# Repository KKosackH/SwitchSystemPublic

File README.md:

# SwitchSystem  
**NOTE: Files with parts under NDA has been removed**

The **SwitchSystem** PCB was developed as an *add-on discharging solution* for existing **AC home chargers**.  

Although the concept worked, the product was ultimately deemed too **expensive** for production. As a result, the design has been made publicly available.  

All major components were tested and verified functional, including the **HomePlug Green PHY (PLC communication)** with negligible switching losses. However, the PCB was not fully finalized — see the [TO-DO](#to-do) list below for pending improvements.  

---

## Features  
- **Discharging add-on** for existing AC chargers  
- **PLC communication** via HomePlug Green PHY  
- **Integration with Raspberry Pi** through a 2×20 GPIO connector  
- **BatteryBridge compatibility** via JST connector  
- **External I/O**: LCD screen and buttons via JST  
- **Vehicle interface**: IEC 62196 Type 2 AC plug with temperature sensor and lock  
- **Inverter interface**: CANBus development board mounted on Raspberry Pi  

---

## Design Notes  
- The board was later split into multiple PCBs to:  
  - Avoid routing **AC mains** directly onto the main board  
  - Reduce **EMI issues**  
- The newer versions (under NDA) added advanced features such as:  
  - **LTE Cat 4 module**  
  - **CANBus support**  
  - **AMD Xilinx Zynq 7000 SoC**  

> ⚠️ If using the **BatteryBridge v2**, remove the `[3.4] DC-DC converter` and patch the **12 V output** of the BatteryBridge to the 12 V net on the SwitchSystem PCB.  

A full circuit description is available in the [Documentation folder](./Documentation).  

---

## Schematic & PCB  

The schematic is organized using hierarchical sheets, with the root page showing all user-interactable components.  

- **First page schematic**  

- **PCB Front**  

- **PCB Back**  

---

## TO-DO  
Remaining improvements for the PCB design:  

1. Add node names to all nets  
2. Ensure all schematic symbols have correct naming  
3. Add transfer vias  
4. Match SPI line lengths  
5. Change BatteryBridge connector to flat-flex  
6. Add new ADC and connect to motor measurement  
7. Add color coding for cables on PCB  
8. Add low-pass filter to CPRead ADC  
9. Add protected earth connector  
10. Add default charge state for power-loss events  
11. Adjust PCB size for mechanically stable Raspberry Pi mounting  

---

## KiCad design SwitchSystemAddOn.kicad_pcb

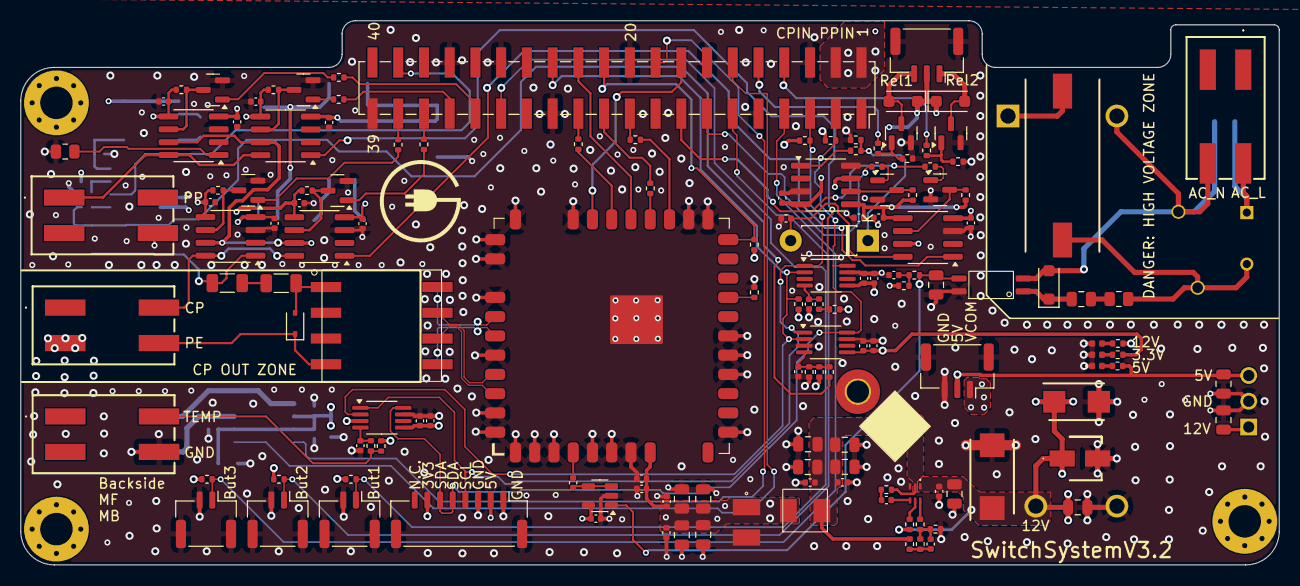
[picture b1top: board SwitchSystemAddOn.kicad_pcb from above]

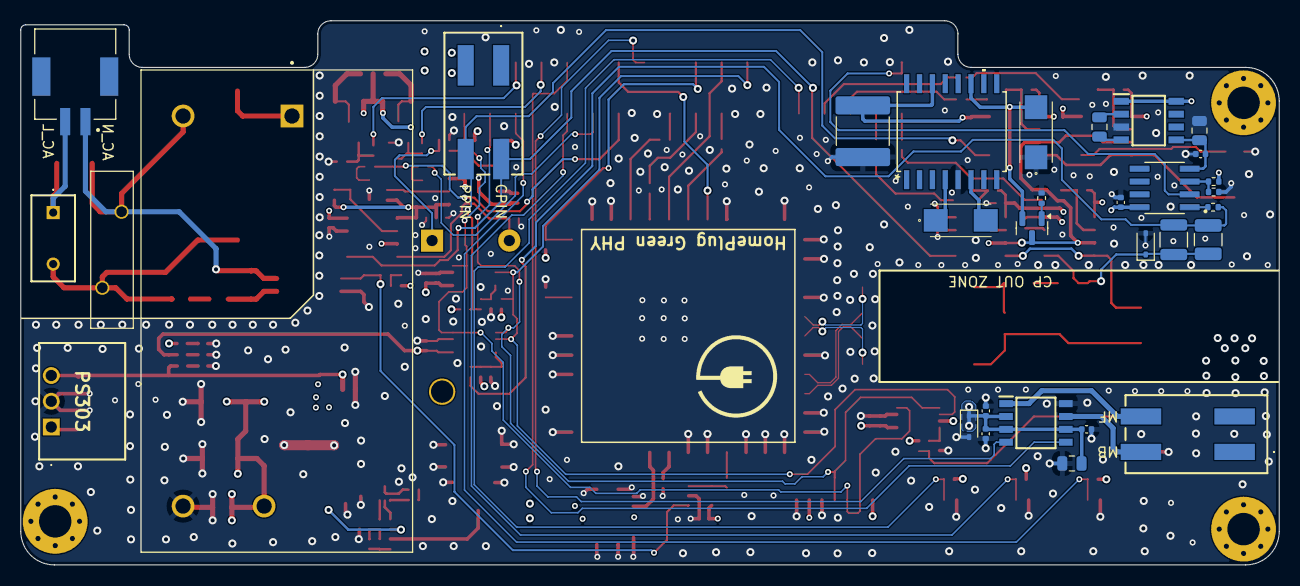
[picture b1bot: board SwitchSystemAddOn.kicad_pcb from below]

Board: 6 copper layers, 124.2 x 53.7 mm, 182 parts (31 on the bottom side), 102 nets.

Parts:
A501: RED-BEET_2.0
C101, C102, C104, C203, C205, C209, C210, C211, C212, C213, C214, C215, C216, C217, C218, C219, C220, C303, C307, C315, C402, C405, C408, C502, C505, C507: 100n; C_0402_1005Metric
C103, C201, C202, C309, C310, C318: 10u; C_0805_2012Metric
C204: 2uF; C_2220_5750Metric
C206, C207: 100uF; T491C
C208, C506: 1n; C_0402_1005Metric
C301: 10u 20% 16V; EEE1AA220WR
C302, C304, C314, C501: 1u 0805; C_0805_2012Metric
C305, C311, C312, C319, C503: 22u; C_0805_2012Metric
C306: 150u; POSCAP_B1_B1S_B1G_B15G_B2_B2S
C308, C317, C504, C508: 1u; C_0402_1005Metric
C313: 10p; C_0402_1005Metric
C316: 22u TANT; CAPPM7343X310N
C401, C404, C407: 470p; C_0402_1005Metric
C403, C406, C409: 4u7; C_0402_1005Metric
C509, C511: 2n2 2kV; C_1206_3216Metric
C510: 220n; C_0805_2012Metric
C512: 2n2 1kV; C_0805_2012Metric
D101, D102, D103: RED; LED_0402_1005Metric
D104, D105: 1N4148W; D_SOD-123F
D106, D201: GBLC12C; D_SOD-323
D202: 1N4934; D_DO-41_SOD81_P7.62mm_Horizontal
D301: SMBJ20A; DIOM5436X261N
D501: GBLC03C; D_SOD-323
D502: SM4007PL; D_SOD-123F
F101: 3.15A; SS5H315AAPH
H101, H102, H103: MH; MountingHole_3.2mm_M3_Pad_Via
H104: MH; MountingHole_2.2mm_M2_Pad_TopOnly
IC201: TC1044SCOA; SOIC127P600X175-8N
IC301: MP1479GTF-Z; MP1479GTFZ
J101, J102, J104, J107, J111, J113: 1412410000
J103: SM02B-PASS-TBT; JST_SM02B-PASS-TBT_LF__SN_
J105, J106, J108: BM02B-GHS-TBT; JST_GH_BM02B-GHS-TBT_1x02-1MP_P1.25mm_Vertical
J109: BM08B-GHS-TBT; JST_GH_BM08B-GHS-TBT_1x08-1MP_P1.25mm_Vertical
J110: 61004021821; PinSocket_2x20_P2.54mm_Vertical_SMD
J112, J114: SM03B-GHS-TB; JST_GH_SM03B-GHS-TB_1x03-1MP_P1.25mm_Horizontal
L201: 220u; L_1210_3225Metric
L301: MPI40; MPI40_Inductor
L302: HER4027; HER4027-100M
M101: BD6231F-E2; SOIC127P620X160-8N
PS301: LD15-23B12R2; CONV_LD15-23B12R2
PS303: R-78K5.0-2.0; R78K5020
Q101, Q103, Q201, Q202, Q203, Q204, Q205, Q206, Q208: MMBT2222A; SOT-23
Q501: HMHA281
R101, R102, R103, R203, R206, R213, R215, R217, R218, R220, R402, R407, R501, R505: 10k 1%; R_0402_1005Metric
R104, R105, R106, R208, R401, R406: 1k 1%; R_0402_1005Metric
R107, R110, R201, R205, R211, R214, R216, R219, R403, R404, R405: 5k1 5%; R_0402_1005Metric
R108, R502, R503, R504: 0R; R_0402_1005Metric
R109, R202, R204, R307: 100k 1%; R_0402_1005Metric
R207: 56k 1%; R_0402_1005Metric
R209: 240k 1%; R_0402_1005Metric
R210: 82k 1%; R_0402_1005Metric
R212: 220R 1%; R_1210_3225Metric
R221: 1k 5%; R_0805_2012Metric
R222: 2K74 1%; R_0402_1005Metric
R223: 1K3 1%; R_0402_1005Metric
R301: 6R8; RESM17073X710N
R302: 47k 1%; R_0402_1005Metric
R303, R306: 10R 1%; R_0402_1005Metric
R304: 40k2 1%; R_0402_1005Metric
R305: 13k 1%; R_0402_1005Metric
R506: 100R 1%; R_0402_1005Metric
R507: 39k 1%; R_0402_1005Metric
R508: 820k 1/3W; R_0805_2012Metric
RV301: B72214S0351K101; VAR_B72214S0131K101
U201: LF353; SOIC127P599X175-8N
U203, U204, U205, U206, U207, U208: ADG417BR; SOIC-8_3.9x4.9mm_P1.27mm
U209: LT1054CSW-PBF; SO-16_SW_LIT
U401, U402, U403: ADC081C021CIMM; MSOP-8_3x3mm_P0.65mm
U501: LM321; SOT-23-5
U502: YT-35636

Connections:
+3V3: A501.8 (VCC), C303.1, C304.1, C305.1, C306.1, C402.1, C403.1, C405.1, C406.1, C408.1, C409.1, C501.1, C502.1, C503.1, C504.1, C505.1, C507.1, J109.7, L301.2, R101.1, R102.1, R103.1, R104.1, R204.2, R207.2, R401.2, R403.2, R404.2, R405.2, R406.2, R501.1, R506.1, U401.5 (VA), U402.5 (VA), U403.3 (ADR0), U403.5 (VA), U501.5 (V+)
+5V: C213.2, C214.2, C215.2, C217.2, C219.2, C220.2, C319.2, J109.2, J114.2, PS303.3 (+VOUT), R105.1, R203.1, R206.1, R213.1, R215.1, R218.1, R220.1, U203.5 (VL), U204.5 (VL), U205.5 (VL), U206.5 (VL), U207.5 (VL), U208.5 (VL)
+12V: C101.1, C102.1, C103.1, C104.1, C204.1, C205.1, C209.2, C210.2, C211.2, C212.2, C216.2, C218.2, C301.1, C302.1, C314.1, C315.1, C316.1, C318.2, D104.1 (K), D105.1 (K), D106.1 (K), D301.1 (A1), IC201.1 (BOOST), IC201.8 (V+), IC301.1 (VIN), J112.2, M101.2 (VCC_1), M101.3 (VCC_2), M101.6 (VREF), PS301.4 (+VO), PS303.1 (+VIN), R106.1, R307.2, U201.8 (V+), U203.4 (V+), U204.4 (V+), U205.4 (V+), U206.4 (V+), U207.4 (V+), U208.4 (V+), U209.14 (V+)
/3V3_Anode: D101.2 (A), R104.2
/5V_Anode: D102.2 (A), R105.2
/12V_Anode: D103.2 (A), R106.2
/AC_DC_Converter/AC_L_IN: PS301.1 (AC(L)), R301.1
/AC_DC_Converter/BST: C317.1, IC301.4 (BST)
/AC_DC_Converter/BUCK_F1: C313.1, R303.1, R304.2
/AC_DC_Converter/BUCK_F2: C313.2, R302.1, R304.1, R305.2
/AC_DC_Converter/BUCK_F3: C317.2, R306.2
/AC_DC_Converter/EN: IC301.5 (EN), R307.1
/AC_DC_Converter/FB: IC301.6 (FB), R302.2
/AC_DC_Converter/OUT_3v3: C307.1, C308.1, C309.1, C310.1, C311.1, C312.1, L301.1, L302.2, R303.2
/AC_DC_Converter/SW: IC301.2 (SW), L302.1, R306.1
/AC_L: F101.2, R301.2, R508.2, RV301.1
/AC_N: D502.2 (A), J103.1, J107.4, PS301.2 (AC(N)), Q501.2 (K), RV301.2
/ADCPPRead/VIN_ADC1: C404.1, R402.2, U402.4 (VIN)
/ADCPPRead/VIN_ADC3: C407.1, R407.2, U403.4 (VIN)
/But1: J105.1, J110.29, R102.2
/But2: J108.1, J110.11, R103.2
/But3: J106.1, J110.7, R101.2
/CP: J104.2, U203.8, U206.8
/CPControl1: J110.35, R211.2
/CPControl2: J110.37, R201.2
/CPIn: J101.2, U205.1, U206.1
/CPQCA: C511.2, D201.1 (K), L201.1, R212.2, U203.1
/CPRead: C401.1, R207.1, R209.1, R210.2, U401.4 (VIN)
/CPSwitchCircuit/6VON: Q204.3 (C), R215.2, U208.6
/CPSwitchCircuit/9VON: Q202.3 (C), R206.2, U205.6
/CPSwitchCircuit/CAP-: C201.2, IC201.4 (CAP-)
/CPSwitchCircuit/CPIN_T: Q203.3 (C), R213.2, U206.6
/CPSwitchCircuit/CPQCA_T: Q201.3 (C), R203.2, U203.6
/CPSwitchCircuit/Cap+: C201.1, IC201.2 (CAP+)
/CPSwitchCircuit/EV9V: D202.1 (K), R222.1, R223.1
/CPSwitchCircuit/EVSIM_IN: C208.1, D202.2 (A), U205.8
/CPSwitchCircuit/OP_DIV: R202.2, R204.1, U201.3 (+)
/CPSwitchCircuit/OP_OUT: R208.1, U201.1
/CPSwitchCircuit/OP_VIN-: C202.2, C203.1, IC201.5 (VOUT), U201.4 (V-)
/CPSwitchCircuit/PPGEN_T: Q208.3 (C), R220.2, U207.6
/CPSwitchCircuit/PPIN_T: Q205.3 (C), R218.2, U204.6
/CPSwitchCircuit/PWM_OUT: L201.2, R208.2, R209.2, R212.1
/CPSwitchCircuit/VOUT_CPUMP: Q206.3 (C), U203.7 (V-), U204.7 (V-), U205.7 (V-), U206.7 (V-), U207.7 (V-), U208.7 (V-)
/CS: A501.25 (CS_/_GPIO_6), J110.24
/FIN: J110.18, M101.4 (FIN)
/INT: A501.27 (INT_/_GPIO_4), J110.16
/InRelay1: D104.2 (A), J112.1, Q103.3 (C)
/InRelay2: D105.2 (A), J112.3, Q101.3 (C)
/Interrupt: J110.26, R403.1, U401.2 (ALERT), U402.2 (ALERT), U403.2 (ALERT)
/MISO: J110.21, R503.1
/MOSI: J110.19, R504.1
/OUT_M1: J111.4, M101.1 (OUT1)
/OUT_M2: J111.2, M101.7 (OUT2)
/PE: D501.1 (K), J104.4, U502.4
/PP: J102.1, U204.8, U207.8
/PPControl1: J110.31, R219.2
/PPControl2: J110.33, R216.2
/PPIn: J101.4, R401.1, R402.1, U204.1
/PWMCP: J110.38, U201.2 (-)
/RIN: J110.12, M101.5 (RIN)
/RST_YB: A501.20 (RESETN), J110.22, R501.2
/RedBeet/A_AC_L: C512.1, D502.1 (K), Q501.1 (A)
/RedBeet/CP_P: C509.1, D501.2 (A), U502.1
/RedBeet/GPIO1_B: A501.17 (GPIO_1), R505.1
/RedBeet/INV_BUFF: C506.2, U501.3 (-), U501.4
/RedBeet/MISO_B: A501.24 (MISO), R503.2
/RedBeet/MOSI_B: A501.23 (MOSI), R504.2
/RedBeet/RX_N: A501.33 (RXN), U502.8
/RedBeet/RX_P: A501.34 (RXP), U502.5
/RedBeet/SCLK_B: A501.26 (SCLK), R502.2
/RedBeet/TX_N: A501.36 (TXN), U502.7
/RedBeet/TX_P: A501.37 (TXP), U502.6
/RedBeet/V_DIV: C508.1, R506.2, R507.1
/RedBeet/ZC_IN: A501.4 (ZC_IN), C506.1
/RedBeet/ZC_OPTO: C510.1, Q501.4 (C), R507.2, U501.1 (+)
/RelayCont1: J110.10, R110.1
/RelayCont2: J110.8, R107.1
/SCL: J109.4, J110.5, R405.1, U401.1 (SCL), U402.1 (SCL), U403.1 (SCL)
/SCLK: J110.23, R502.1
/SDA: J109.5, J109.6, J110.3, R404.1, U401.8 (SDA), U402.8 (SDA), U403.8 (SDA)
/SimReady: J110.13, R214.2
/SimSwitch: J110.15, R205.2
/TEMP_SENSE: J113.2, R406.1, R407.1
GND: A501.1 (GND), A501.2 (GND), A501.3 (GND), A501.5 (GND), A501.6 (GND), A501.7 (GND), A501.10 (GND), A501.13 (EPHY_RX_N), A501.14 (EPHY_RX_P), A501.15 (GND), A501.21 (GND), A501.22 (GND), A501.28 (GND), A501.29 (GND), A501.30 (GND), A501.31 (GND), A501.32 (GND), A501.35 (GND), A501.38 (GND), A501.39 (GND), A501.40 (TPAD), C101.2, C102.2, C103.2, C104.2, C202.1, C203.2, C204.2, C205.2, C207.1, C208.2, C209.1, C210.1, C211.1, C212.1, C213.1, C214.1, C215.1, C216.1, C217.1, C218.1, C219.1, C220.1, C301.2, C302.2, C303.2, C304.2, C305.2, C306.2, C307.2, C308.2, C309.2, C310.2, C311.2, C312.2, C314.2, C315.2, C316.2, C318.1, C319.1, C401.2, C402.2, C403.2, C404.2, C405.2, C406.2, C407.2, C408.2, C409.2, C501.2, C502.2, C503.2, C504.2, C505.2, C507.2, C508.2, C510.2, D101.1 (K), D102.1 (K), D103.1 (K), D106.2 (A), D201.2 (A), D301.2 (A2), IC201.3 (GND), IC301.3 (GND), J104.3, J105.2, J105.MP (MountPin), J106.2, J106.MP (MountPin), J108.2, J108.MP (MountPin), J109.1, J109.3, J109.MP (MountPin), J110.6, J110.9, J110.14, J110.20, J110.25, J110.30, J110.34, J110.39, J112.MP (MountPin), J113.4, J114.3, J114.MP (MountPin), M101.8 (GND), PS301.3 (-VO), PS303.2 (GND), Q101.2 (E), Q103.2 (E), Q201.2 (E), Q202.2 (E), Q203.2 (E), Q204.2 (E), Q205.2 (E), Q208.2 (E), Q501.3 (E), R108.1, R109.2, R202.1, R210.1, R217.2, R221.1, R222.2, R305.1, R505.2, U203.3 (GND), U204.3 (GND), U205.3 (GND), U206.3 (GND), U207.3 (GND), U208.3 (GND), U208.8, U209.5 (GND), U401.3 (ADR0), U401.7 (GND), U402.7 (GND), U403.7 (GND), U501.2 (V-)
unnamed: C509.2, C511.1
unnamed: C512.2, R508.1
unnamed: F101.1, J103.2, J107.2
unnamed: Q101.1 (B), R109.1, R110.2
unnamed: Q103.1 (B), R107.2, R108.2
unnamed: Q201.1 (B), R201.1
unnamed: Q202.1 (B), R205.1
unnamed: Q203.1 (B), R211.1
unnamed: Q204.1 (B), R214.1
unnamed: Q205.1 (B), R216.1
unnamed: Q206.1 (B), R217.1
unnamed: C207.2, Q206.2 (E), U209.11 (VOUT)
unnamed: Q208.1 (B), R219.1
unnamed: R221.2, U207.1
unnamed: R223.2, U208.1
unnamed: C206.1, U209.4 (CAP+)
unnamed: C206.2, U209.6 (CAP-)
VCOM: J110.2, J110.4, J114.1

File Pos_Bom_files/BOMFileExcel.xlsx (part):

Reference | Value | Datasheet | Footprint | Description | Qty | DNP | Manufacturer_Name | Manufacturer_Part_Number | Generic | Supplier link
U502 | YT-35636 | ~ | Footprints:YT-35636 | Power Line Communication Transformer YT-35636 (292877) | 1 |  | Codico | 292877 | No | https://www.codico.com/en/yt-35636-292877
U501 | LM321 | http://www.ti.com/lit/ds/symlink/lm321.pdf | Package_TO_SOT_SMD:SOT-23-5 | Low Power Single Operational Amplifier, SOT-23-5 | 1 |  | Texas Instruments | LM321LVIDCKR | No | https://www.mouser.dk/ProductDetail/STMicroelectronics/LMV32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
U401,U402,U403 | ADC081C021CIMM | http://www.ti.com/lit/ds/symlink/adc081c021.pdf | Package_SO:MSOP-8_3x3mm_P0.65mm | IC ADC 8BIT SAR 8VSSOP | 3 |  | Texas Instruments | ADC081C021CIMM/NOPB | No | https://www.digikey.dk/en/products/detail/texas-instruments/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
U209 | LT1054CSW-PBF | LT1054CSW-PBF | Footprints:SO-16_SW_LIT | IC REG CHARG PUMP INV 16SOIC | 1 |  | Analog Devices Inc. | LT1054CSW#PBF | No | https://www.digikey.dk/en/products/detail/analog-devices-inc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
U203,U204,U205,U206,U207,U208 | ADG417BR | https://www.analog.com/media/en/technical-documentation/data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 | Package_SO:SOIC-8_3.9x4.9mm_P1.27mm | Single SPST Monolithic LC²MOS Analog Switch, normally OFF, 35Ohm Ron, SOIC-8 | 6 |  | Analog Devices Inc. | ADG417BR | No | https://www.digikey.dk/en/products/detail/analog-devices-inc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
U201 | LF353 | ~ | Footprints:SOIC127P599X175-8N | IC OPAMP GP 2 CIRCUIT 8SOIC | 1 |  | Texas Instruments | LF353MX/NOPB | No | https://www.digikey.dk/en/products/detail/texas-instruments/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
RV301 | B72214S0351K101 | ~ | Footprints:VAR_B72214S0131K101 | VARISTOR DISC 14MM | 1 |  | EPCOS - TDK Electronics | B72214S0351K101 | No | https://www.digikey.dk/en/products/detail/epcos-tdk-electron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
R508 | 820k 1/3W | ~ | Resistor_SMD:R_0805_2012Metric | 820K OHM 1% 1/3W 0805 | 1 |  | ~ | ~ | Yes | ~
R507 | 39k 1% | ~ | Resistor_SMD:R_0402_1005Metric | 39K OHM 1% 1/16W 0402 | 1 |  | ~ | ~ | Yes | ~
R506 | 100R 1% | ~ | Resistor_SMD:R_0402_1005Metric | 100 OHM 1% 1/16W 0402 | 1 |  | ~ | ~ | Yes | ~
R502,R503,R504 | 0R | ~ | Resistor_SMD:R_0402_1005Metric | 0R 1/16W 0402 | 3 |  | ~ | ~ | Yes | ~
R305 | 13k 1% | ~ | Resistor_SMD:R_0402_1005Metric | 13K OHM 1% 1/16W 0402 | 1 |  | ~ | ~ | Yes | ~
R304 | 40k2 1% | ~ | Resistor_SMD:R_0402_1005Metric | 40.2K OHM 1% 1/16W 0402 | 1 |  | ~ | ~ | Yes | ~
R303,R306 | 10R 1% | ~ | Resistor_SMD:R_0402_1005Metric | 10 OHM 1% 1/16W 0402 | 2 |  | ~ | ~ | Yes | ~
R302 | 47k 1% | ~ | Resistor_SMD:R_0402_1005Metric | 47K OHM 1% 1/16W 0402 | 1 |  | ~ | ~ | Yes | ~
R301 | 6R8 | ~ | Footprints:RESM17073X710N | SMQW3W 6R8 5% | 1 |  | TE Connectivity Passive Product | SMQW36R8JT | No | https://www.digikey.dk/en/products/detail/te-connectivity-pa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
R223 | 1K3 1% | ~ | Resistor_SMD:R_0402_1005Metric | 1300 OHM 1% 1/16W 0402 | 1 |  | ~ | ~ | Yes | ~
R222 | 2K74 1% | ~ | Resistor_SMD:R_0402_1005Metric | 2.74K OHM 1% 1/16W 0402 | 1 |  | ~ | ~ | Yes | ~
R221 | 1k 5% | ~ | Resistor_SMD:R_0805_2012Metric | ~ | 1 | DNP | ~ | ~ | ~ | ~
R212 | 220R 1% | ~ | Resistor_SMD:R_1210_3225Metric | 220 OHM 1% 1/2W 1210 | 1 |  | ~ | ~ | Yes | ~
R210 | 82k 1% | ~ | Resistor_SMD:R_0402_1005Metric | 82K OHM 1% 1/16W 0402 | 1 |  | ~ | ~ | Yes | ~
R209 | 240k 1% | ~ | Resistor_SMD:R_0402_1005Metric | 240K OHM 1% 1/16W 0402 | 1 |  | ~ | ~ | Yes | ~
R207 | 56k 1% | ~ | Resistor_SMD:R_0402_1005Metric | 56K OHM 1% 1/16W 0402 | 1 |  | ~ | ~ | Yes | ~
R202,R204,R307 | 100k 1% | ~ | Resistor_SMD:R_0402_1005Metric | 100K OHM 1% 1/16W 0402 | 3 |  | ~ | ~ | Yes | ~
R109 | 100k 1% | ~ | Resistor_SMD:R_0402_1005Metric | ~ | 1 | DNP | ~ | ~ | ~ | ~
R108 | 0R | ~ | Resistor_SMD:R_0402_1005Metric | ~ | 1 | DNP | ~ | ~ | ~ | ~
R107,R110,R201,R205,R211,R214,R216,R219,R403,R404,R405 | 5k1 5% | ~ | Resistor_SMD:R_0402_1005Metric | 5.1K OHM 5% 1/16W 0402 | 11 |  | ~ | ~ | Yes | ~
R104,R105,R106,R208,R401,R406 | 1k 1% | ~ | Resistor_SMD:R_0402_1005Metric | 1K OHM 1% 1/16W 0402 | 6 |  | ~ | ~ | Yes | ~
R101,R102,R103,R203,R206,R213,R215,R217,R218,R220,R402,R407,R501,R505 | 10k 1% | ~ | Resistor_SMD:R_0402_1005Metric | 10K OHM 1% 1/16W 0402 | 14 |  | ~ | ~ | Yes | ~
Q501 | HMHA281 | https://www.onsemi.com/pub/Collateral/HMHA2801B-D.PDF | Footprints:HMHA281 | Transistor Output Optocouplers Optocoupler Phototransistor | 1 |  | onsemi | HMHA281 | No | https://www.digikey.dk/en/products/detail/onsemi/HMHA281/1051345
Q101,Q103,Q201,Q202,Q203,Q204,Q205,Q206,Q208 | MMBT2222A | ~ | Package_TO_SOT_SMD:SOT-23 | BJT SOT-23 40V 600MA | 9 |  | Diotec Semiconductor | MMBT2222A | No | https://www.digikey.dk/en/products/detail/diotec-semiconduct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
PS303 | R-78K5.0-2.0 | https://recom-power.com/pdf/Innoline/R-78K-2.0.pdf | Footprints:R78K5020 | 2.0 Amp SIP3 Single Output | 1 |  | RECOM Power | R-78K5.0-2.0 | No | https://www.mouser.dk/ProductDetail/RECOM-Power/R-78K50-20?q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
PS301 | LD15-23B12R2 | ~ | Footprints:CONV_LD15-23B12R2 | AC/DC PCB Mount Power Supply (PSU), 100 to 430VDC, ITE, Household & Medical, 1 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 | 1 |  | MULTICOMP PRO | MP-LD15-23B12R2 | No | https://dk.farnell.com/multicomp-pro/mp-ld15-23b12r2/power-s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
M101 | BD6231F-E2 | https://componentsearchengine.com/Datasheets/2/BD6231F-E2.pdf | Footprints:SOIC127P620X160-8N | H-Bridge motor driver,36V,1A,SOP8 ROHM BD6231F-E2 Full Bridge Motor Driver 1A, 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 | 1 |  | ROHM Semiconductor | BD6231F-E2 | No | https://www.digikey.dk/en/products/detail/rohm-semiconductor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
L302 | HER4027 | ~ | HER4027-100M:HER4027-100M | HER4027-100M-R | 1 |  | SAGAMI | 269533 | No | https://www.codico.com/en/her4027-100m-r
L301 | MPI40 | ~ | MPI40_Inductor:MPI40_Inductor | MPIA4015V2-R22-R | 1 |  | EATON ELECTRONICS | 289754 | No | https://www.codico.com/en/mpia4015v2-r22-r
L201 | 220u | ~ | Inductor_SMD:L_1210_3225Metric | FIXED IND 220UH 100MA 10.9OHM SM | 1 |  | EPCOS - TDK Electronics | B82422H1224K000 | No | https://www.digikey.com/en/products/detail/epcos-tdk-electro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
J112,J114 | SM03B-GHS-TB | ~ | Connector_JST:JST_GH_SM03B-GHS-TB_1x03-1MP_P1.25mm_Horizontal | CONN HEADER SMD R/A 3POS 1.25MM | 2 |  | JST Sales America Inc. | SM03B-GHS-TB | Yes | https://www.digikey.dk/en/products/detail/jst-sales-america-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
J110 | 61004021821 | ~ | Connector_PinSocket_2.54mm:PinSocket_2x20_P2.54mm_Vertical_SMD | WR-PHD 2.54 MM DUAL SMT SOCKET H | 1 |  | Würth Elektronik | 61004021821 | Yes | https://www.digikey.dk/en/products/detail/w%C3%BCrth-elektro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
J109 | BM08B-GHS-TBT | ~ | Connector_JST:JST_GH_BM08B-GHS-TBT_1x08-1MP_P1.25mm_Vertical | CONN HEADER SMD 8POS 1.25MM | 1 |  | JST Sales America Inc. | BM08B-GHS-TBT | Yes | https://www.digikey.dk/en/products/detail/jst-sales-america-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
J105,J106,J108 | BM02B-GHS-TBT | ~ | Connector_JST:JST_GH_BM02B-GHS-TBT_1x02-1MP_P1.25mm_Vertical | CONN HEADER SMD 2POS 1.25MM | 3 |  | JST Sales America Inc. | BM02B-GHS-TBT | Yes | https://www.digikey.dk/en/products/detail/jst-sales-america-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
J103 | SM02B-PASS-TBT | ~ | Footprints:JST_SM02B-PASS-TBT_LF__SN_ | CONN HEADER SMD R/A 2POS 2MM | 1 |  | JST Sales America Inc. | SM02B-PASS-TBT | Yes | https://www.digikey.dk/en/products/detail/jst-sales-america-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
J101,J102,J104,J107,J111,J113 | 1412410000 | https://catalog.weidmueller.com/catalog/Start.do;jsessionid=2545CA0BAB23962A974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 | Footprints:1412410000 | Printed circuit board terminals, 3.50 mm, Number of poles: 2, 90, black, PUSH I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 | 6 |  | Weidmuller | 1412410000 | No | https://eu.mouser.com/ProductDetail/Weidmuller/1412410000?qs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
IC301 | MP1479GTF-Z | https://www.mouser.jp/datasheet/2/277/MP1479-1578710.pdf | Footprints:MP1479GTFZ | Switching Voltage Regulators 1A, 3.9-18V, 800kHz, High-Efficiency, Synchronous,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 | 1 |  | Monolithic Power Systems (MPS) | MP1479GTF-Z | No | https://www.digikey.dk/en/products/detail/monolithic-power-s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
IC201 | TC1044SCOA | https://datasheet.datasheetarchive.com/originals/distributor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 | Footprints:SOIC127P600X175-8N | IC REG CHARG PUMP INV 20MA 8SOIC | 1 |  | Microchip Technology | TC1044SCOA | No | https://www.digikey.dk/en/products/detail/microchip-technolo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

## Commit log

2025-10-05 Pushed public version of SwitchSystem
2025-10-05 Removed NDA parts from docs
